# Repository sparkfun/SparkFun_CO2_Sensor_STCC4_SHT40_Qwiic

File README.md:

# SparkFun Qwiic CO₂ Sensor - STCC4

The SparkFun Qwiic CO₂ Sensor - STCC4 is a compact, plug-and-play air quality breakout built around the STCC4 CO₂ sensor paired with a Sensirion SHT41 temperature and humidity sensor for on-board environmental compensation. Connect via the Qwiic connector or the PTH header (GND, 3V3, SDA, SCL) and start reading calibrated CO₂ concentrations, temperature, and relative humidity over I2C in minutes — no external components required.

Designed for our [Qwiic ecosystem](https://www.sparkfun.com/qwiic), this 1" × 1" board plugs straight into any Qwiic-enabled microcontroller. A power LED confirms operation at a glance, and the four mounting holes make permanent installation straightforward. Whether you are monitoring indoor air quality, building a ventilation controller, or logging CO₂ trends in a greenhouse or classroom, the STCC4 delivers accurate, temperature- and humidity-compensated readings in a breadboard-friendly package.

## Repository Contents

* **/docs** - Documentation files for GitHub pages
* **/Documents** - Datasheets, additional product information
* **/Hardware** - KiCad design files (.kicad_sch, .kicad_pcb)
* **/Production** - Production panel files

## Documentation

* **[Library](https://github.com/sparkfun/SparkFun_STCC4_Arduino_Library)** - Arduino library for the SparkFun Qwiic CO₂ Sensor - STCC4.
* **[Hookup Guide](https://docs.sparkfun.com/SparkFun_Qwiic_CO2_Sensor_STCC4/)** - Basic hookup guide for the SparkFun Qwiic CO₂ Sensor - STCC4.

## Product Versions

* **[SEN-XXXXX](https://www.sparkfun.com/products/XXXXX)** - Initial release of the SparkFun Qwiic CO₂ Sensor - STCC4.

## License Information

This product is _**open source**_!

Please review the LICENSE.md file for license information.

If you have any questions or concerns about licensing, please contact technical support on our [SparkFun forums](https://forum.sparkfun.com/viewforum.php?f=152).

Distributed as-is; no warranty is given.

_- Your friends at SparkFun._

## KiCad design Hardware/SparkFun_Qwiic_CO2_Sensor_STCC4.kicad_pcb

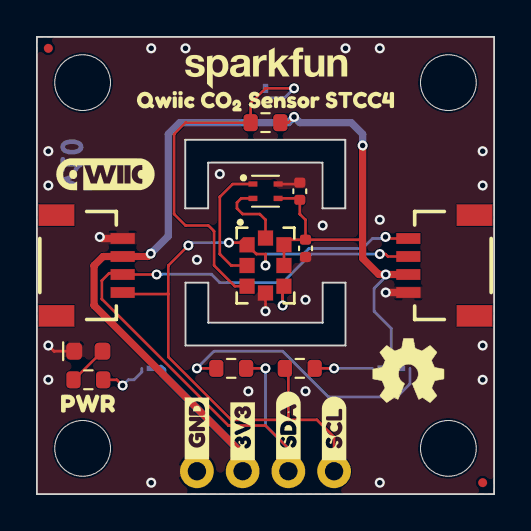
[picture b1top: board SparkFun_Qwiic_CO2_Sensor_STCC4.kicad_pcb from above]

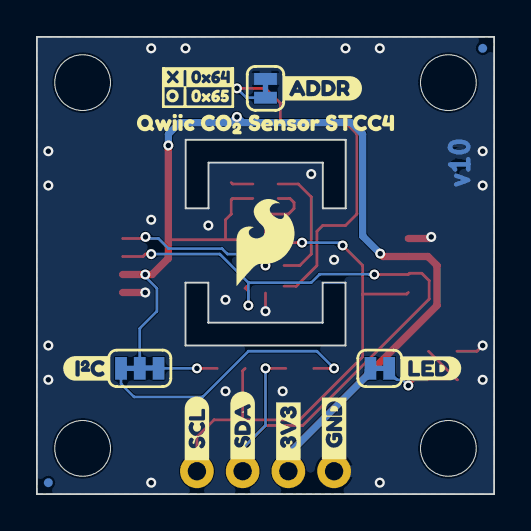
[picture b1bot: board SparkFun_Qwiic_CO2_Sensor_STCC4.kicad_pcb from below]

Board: 2 copper layers, 25.4 x 25.4 mm, 43 parts (16 on the bottom side), 11 nets.

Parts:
C10, C11: 0.1uF; C_0402_1005Metric
D1: Red; LED_0603_1608Metric_Red
FID1, FID2, FID3, FID4: Fiducial_0.5mm; Fiducial_0.5mm_Mask1mm
G4: OSHW_Logo; Creative_Commons_License
J1, J2: Qwiic_RA; JST_1x04_P1.0mm_Horizontal_SMD
J3: Conn_01x06; 1x04_P2.54mm
JP1: LED; Jumper_2_NC_Trace
JP2: I²C; Jumper_3_NC-2_Trace
JP3: ADDR; Jumper_2_NC_Trace
R3, R6: 4.7k; R_0603_1608Metric
R4, R5: 2.2k; R_0603_1608Metric
Ref**: Val**; OSHW_Logo_4mm
ST1, ST2, ST3, ST4: Standoff
U2: STCC4
U3: SHT40; Sensirion_DFN-4_1.5x1.5mm_P0.8mm_SHT4x_NoCentralPad
kibuzzard-6A0B3951: G***; kibuzzard-6A0B3951
kibuzzard-6A0B3970: G***; kibuzzard-6A0B3970
kibuzzard-6A063CE8: G***; kibuzzard-6A063CE8
kibuzzard-6A079B3E, kibuzzard-6A079B3E#2: G***; kibuzzard-6A079B3E
kibuzzard-6A079B36, kibuzzard-6A079B36#2: G***; kibuzzard-6A079B36
kibuzzard-6A07969C: G***; kibuzzard-6A07969C
kibuzzard-689A66E2: G***; kibuzzard-689A66E2
kibuzzard-689A66E9: G***; kibuzzard-689A66E9
kibuzzard-689A66EE: G***; kibuzzard-689A66EE
kibuzzard-689A66F4: G***; kibuzzard-689A66F4
kibuzzard-689A642E: G***; kibuzzard-689A642E
kibuzzard-689A6711: G***; kibuzzard-689A6711
kibuzzard-689A6718: G***; kibuzzard-689A6718
kibuzzard-689A6721: G***; kibuzzard-689A6721
kibuzzard-689A6728: G***; kibuzzard-689A6728
kibuzzard-689A6796: G***; kibuzzard-689A6796

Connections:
3.3V: C10.1, C11.1, J1.2, J2.2, J3.2, JP1.2 (B), JP2.2 (B), R6.2, U2.6 (VDD_IO), U2.7 (VDD), U3.3 (VDD)
ADDR: JP3.2 (B), R6.1, U2.3 (ADDR)
GND: C10.2, C11.2, D1.1 (K), J1.1, J2.1, J3.1, JP3.1 (A), U2.4 (GND), U3.4 (VSS)
unnamed: D1.2 (A), R3.1
unnamed: JP1.1 (A), R3.2
unnamed: JP2.1 (A), R5.1
unnamed: JP2.3 (C), R4.1
unnamed: U2.8 (SCL_C), U3.2 (SCL)
unnamed: U2.2 (SDA_C), U3.1 (SDA)
SCL: J1.4, J2.4, J3.4, R4.2, U2.1 (SCL)
SDA: J1.3, J2.3, J3.3, R5.2, U2.5 (SDA)

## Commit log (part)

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2026-05-18 Finalized the Silkscreen
2026-05-18 Adds gitignore
2026-05-19 Added changes from Design Review
    - Nudged vias
    - Replaced "pullup" capacitors
    - Adjusted measures alignment
    - Adjusted solder paste expansion
    - Swapped Flame and OSHW Logos
2026-05-19 Moved I2C Address Table
2026-05-19 Remove gitignore files
2026-05-22 Updates Edge Cut polygon to an outline and adds "Route Out" to ensure proper manufacturing

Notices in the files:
parts and their libraries:
Released under the Creative Commons Attribution Share-Alike 4.0 License
https://creativecommons.org/licenses/by-sa/4.0
